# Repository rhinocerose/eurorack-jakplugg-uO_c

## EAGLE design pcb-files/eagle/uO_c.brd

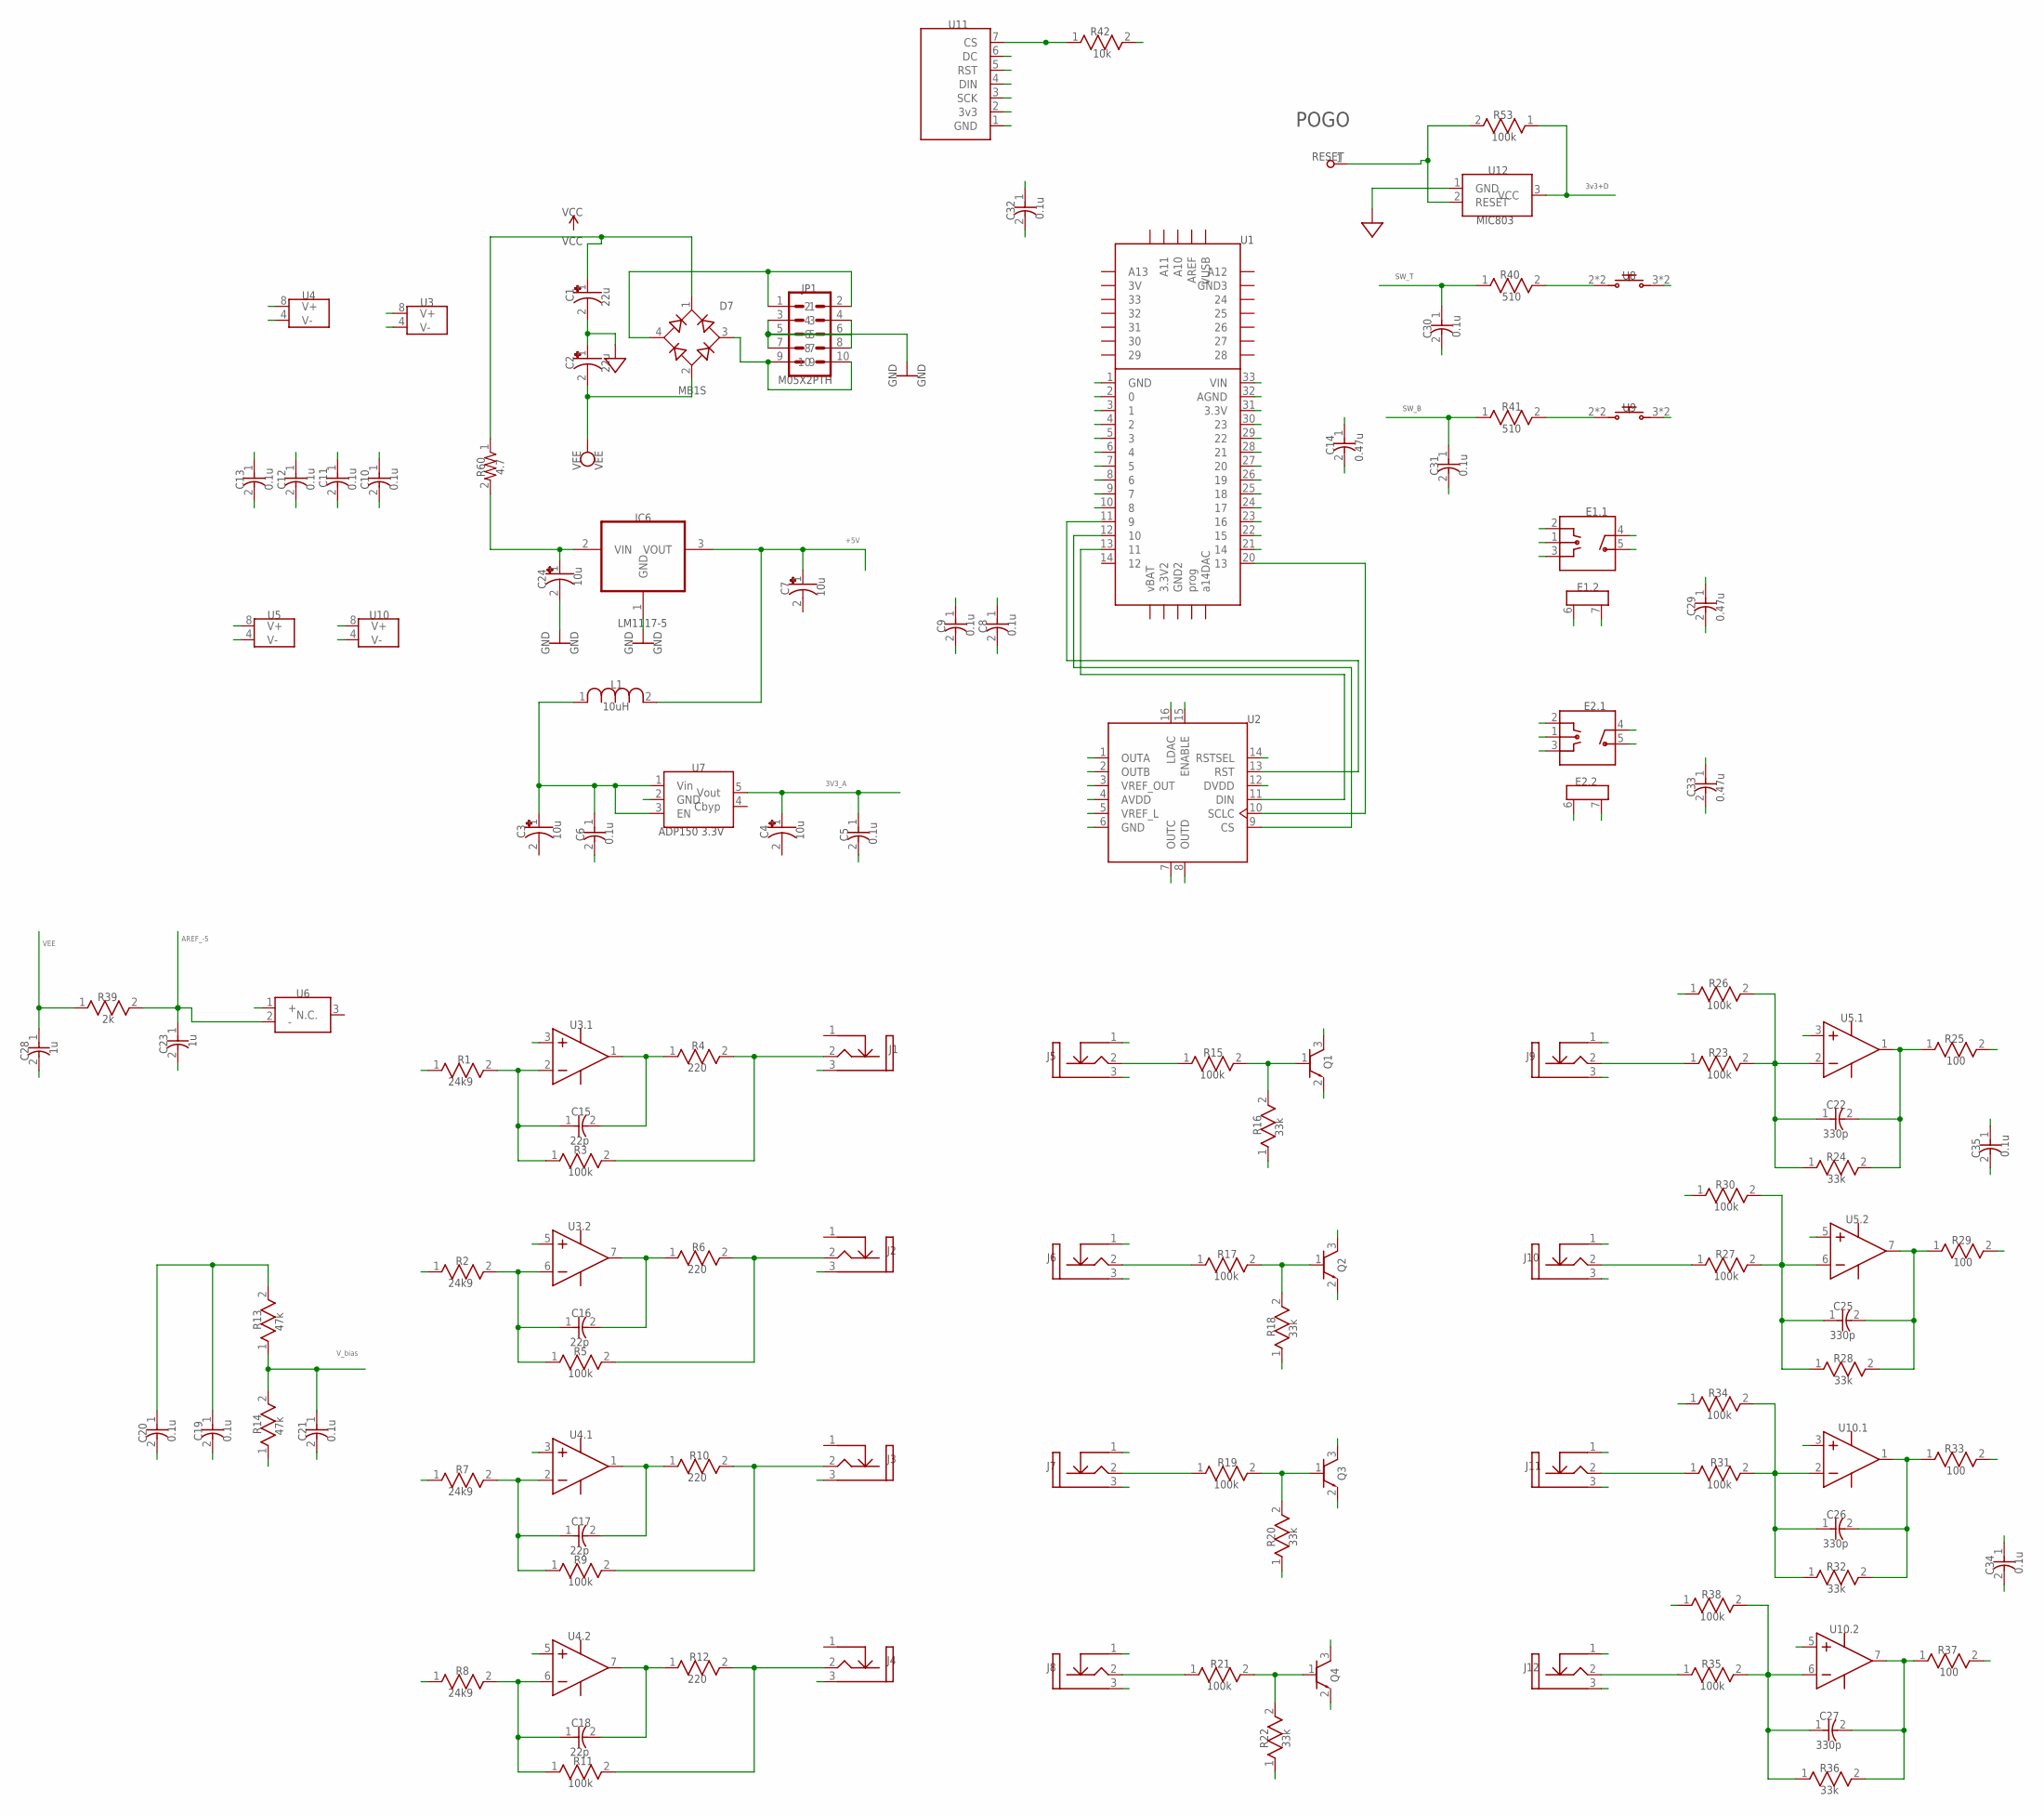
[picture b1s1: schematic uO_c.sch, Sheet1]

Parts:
C1, C2: 22u; CAPAE-5.3X5.3H3
C3, C4, C7, C24: 10u; CAPAE-5.3X5.3H3
C5, C6, C8, C9, C10, C11, C12, C13, C19, C20, C21, C30, C31, C32, C34, C35: 0.1u; CAP_0805
C14, C29, C33: 0.47u; CAP_0805
C15, C16, C17, C18: 22p; CAP_0805
C22, C25, C26, C27: 330p; CAP_0805
C23, C28: 1u; CAP_0805
D7: MB1S; SOP-4/6.5X2.54
E1, E2: PEC11
IC6: LM1117-5; TO252
J1, J2, J3, J4: THONKICONN; THONKICONN_JACK
J5, J6, J7, J8, J9, J10, J11, J12: THONKICONN_20; THONKICONN_JACK
JP1: M05X2PTH; AVR_ICSP
L1: 10uH; RES_1210
Q1, Q2, Q3, Q4: MMBT3904; SOT23
R1, R2, R7, R8: 24k9; RES_0805
R3, R5, R9, R11, R15, R17, R19, R21, R23, R26, R27, R30, R31, R34, R35, R38, R53: 100k; RES_0805
R4, R6, R10, R12: 220; RES_0805
R13, R14: 47k; RES_0805
R16, R18, R20, R22, R24, R28, R32, R36: 33k; RES_0805
R25, R29, R33, R37: 100; RES_0805
R39: 2k; RES_0805
R40, R41: 510; RES_0805
R42: 10k; RES_0805
R60: 4.7; R1206
RESET: RESET; ROUND-ROUND
U1: TEENSY_3.1_EDGE; TEENSY3.1_EDGE
U2: DAC8565; TSSOP-16
U3, U4: OPA2172; SOIC-8/150MIL
U5, U10: MCP6002; SOIC-8/150MIL
U6: LM4040_EM3-5.0; SOT23
U7: ADP150 3.3V; SOT23-5
U8, U9: 6MM_TACTILE_SW; TL1105SP
U11: 1306_DISP_O_C
U12: MIC803; SOT23

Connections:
3V3_A: C4.1 (+), C5.1, C9.1, C34.1, C35.1, U2.4 (AVDD), U5.8 (V+), U7.5 (Vout), U10.8 (V+)
3v3+D: C8.1, C14.1, C32.1, R42.2, R53.1, U1.31 (3.3V), U2.12 (DVDD), U11.2 (3v3), U12.3 (VCC)
+5V: C7.1 (+), IC6.3 (VOUT), L1.2, U1.33 (VIN)
AREF_-5: C23.1, R26.1, R30.1, R34.1, R38.1, R39.2, U6.2 (-)
CS_DAC: U1.12 (10), U2.9 (CS)
CS_OLED: R42.1, U1.10 (8), U11.7 (CS)
CV_1: R25.2, U1.26 (19)
CV_2: R29.2, U1.25 (18)
CV_3: R33.2, U1.27 (20)
CV_4: R37.2, U1.24 (17)
CV_A: R1.1, U2.1 (OUTA)
CV_B: R2.1, U2.2 (OUTB)
CV_C: R7.1, U2.7 (OUTC)
CV_D: R8.1, U2.8 (OUTD)
DC: U1.8 (6), U11.6 (DC)
DOUT: U1.13 (11), U2.11 (DIN), U11.4 (DIN)
ENC_L1: E1.2, U1.29 (22)
ENC_L2: E1.3, U1.28 (21)
ENC_R1: E2.2, U1.22 (15)
ENC_R2: E2.3, U1.23 (16)
GND: C1.2 (-), C2.1 (+), C3.2 (-), C4.2 (-), C5.2, C6.2, C7.2 (-), C8.2, C9.2, C10.2, C11.2, C12.1, C13.1, C14.2, C19.2, C20.2, C21.2, C23.2, C24.2 (-), C28.2, C29.2, C30.2, C31.2, C32.2, C33.2, C34.2, C35.2, E1.1, E1.5, E1.6 (gnd), E1.7 (gnd), E2.1, E2.5, E2.6 (gnd), E2.7 (gnd), IC6.1 (GND), J1.3 (GND), J2.3 (GND), J3.3 (GND), J4.3 (GND), J5.1 (TN), J5.3 (GND), J6.1 (TN), J6.3 (GND), J7.1 (TN), J7.3 (GND), J8.1 (TN), J8.3 (GND), J9.1 (TN), J9.3 (GND), J10.1 (TN), J10.3 (GND), J11.1 (TN), J11.3 (GND), J12.1 (TN), J12.3 (GND), JP1.3, JP1.4, JP1.5, JP1.6, JP1.7, JP1.8, Q1.2 ((E)), Q2.2 ((E)), Q3.2 ((E)), Q4.2 ((E)), R14.1, R16.1, R18.1, R20.1, R22.1, U1.1 (GND), U1.32 (AGND), U2.5 (VREF_L), U2.6 (GND), U2.14 (RSTSEL), U2.15 (ENABLE), U2.16 (LDAC), U5.3 (IN+), U5.4 (V-), U5.5 (IN+), U6.1 (+), U7.2 (GND), U8.3 (2), U8.4 (2), U9.3 (2), U9.4 (2), U10.3 (IN+), U10.4 (V-), U10.5 (IN+), U11.1 (GND), U12.1 (GND)
unnamed: D7.3 (AC2), JP1.9, JP1.10
Net_0: J2.2 (Tip), R5.2, R6.2
Net_1: C16.1, R2.2, R5.1, U3.6 (IN-)
Net_2: C16.2, R6.1, U3.7 (OUT)
Net_3: J3.2 (Tip), R9.2, R10.2
Net_4: C17.1, R7.2, R9.1, U4.2 (IN-)
Net_5: C17.2, R10.1, U4.1 (OUT)
Net_6: J4.2 (Tip), R11.2, R12.2
Net_7: C18.1, R8.2, R11.1, U4.6 (IN-)
Net_8: C18.2, R12.1, U4.7 (OUT)
Net_9: Q2.1 ((B)), R17.2, R18.2
Net_10: Q3.1 ((B)), R19.2, R20.2
Net_11: Q4.1 ((B)), R21.2, R22.2
Net_12: C25.1, R27.2, R28.1, R30.2, U5.6 (IN-)
Net_13: C3.1 (+), C6.1, L1.1, U7.1 (Vin), U7.3 (EN)
Net_18: C26.1, R31.2, R32.1, R34.2, U10.2 (IN-)
Net_19: J1.2 (Tip), R3.2, R4.2
Net_20: C15.1, R1.2, R3.1, U3.2 (IN-)
Net_21: C15.2, R4.1, U3.1 (OUT)
Net_22: C27.1, R35.2, R36.1, R38.2, U10.6 (IN-)
Net_35: Q1.1 ((B)), R15.2, R16.2
Net_39: J8.2 (Tip), R21.1
Net_40: J7.2 (Tip), R19.1
Net_41: J6.2 (Tip), R17.1
Net_42: J5.2 (Tip), R15.1
Net_43: C22.1, R23.2, R24.1, R26.2, U5.2 (IN-)
Net_48: C27.2, R36.2, R37.1, U10.7 (OUT)
Net_49: C26.2, R32.2, R33.1, U10.1 (OUT)
Net_50: C25.2, R28.2, R29.1, U5.7 (OUT)
Net_51: C22.2, R24.2, R25.1, U5.1 (OUT)
Net_52: J9.2 (Tip), R23.1
Net_53: J10.2 (Tip), R27.1
Net_54: J11.2 (Tip), R31.1
Net_55: J12.2 (Tip), R35.1
Net_73: C24.1 (+), IC6.2 (VIN), R60.2
Net_75: R41.2, U9.1, U9.2 (1)
Net_76: R40.2, U8.1, U8.2 (1)
Net_88: R53.2, RESET.1, U12.2 (RESET)
Net_107: D7.4 (AC1), JP1.1, JP1.2
RST: U1.9 (7), U11.5 (RST)
RST_DAC: U1.11 (9), U2.13 (RST)
SCK: U1.20 (13), U2.10 (SCLC), U11.3 (SCK)
SW_B: C31.1, R41.1, U1.6 (4)
SW_L: C29.1, E1.4, U1.30 (23)
SW_R: C33.1, E2.4, U1.21 (14)
SW_T: C30.1, R40.1, U1.7 (5)
TR1: Q1.3 ((C)), U1.2 (0)
TR2: Q2.3 ((C)), U1.3 (1)
TR3: Q3.3 ((C)), U1.4 (2)
TR4: Q4.3 ((C)), U1.5 (3)
VCC: C1.1 (+), C10.1, C11.1, D7.1 (+), R60.1, U3.8 (V+), U4.8 (V+)
VEE: C2.2 (-), C12.2, C13.2, C28.1, D7.2 (-), R39.1, U3.4 (V-), U4.4 (V-)
VREF_2v5: C19.1, C20.1, R13.2, U2.3 (VREF_OUT)
V_bias: C21.1, R13.1, R14.2, U3.3 (IN+), U3.5 (IN+), U4.3 (IN+), U4.5 (IN+)

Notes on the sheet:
SW_T
SW_B
3v3+D
POGO
22u
10u
0.1u
C10
C11
C12
C13
C14
0.47u
C15
22p
C16
C17
C18
C19
C20
C21
C22
330p
C23
C24
C25
C26
C27
C28
C29
C30
C31
C32
MB1S
E1.1
E1.2
E2.1
E2.2
GND
IC6

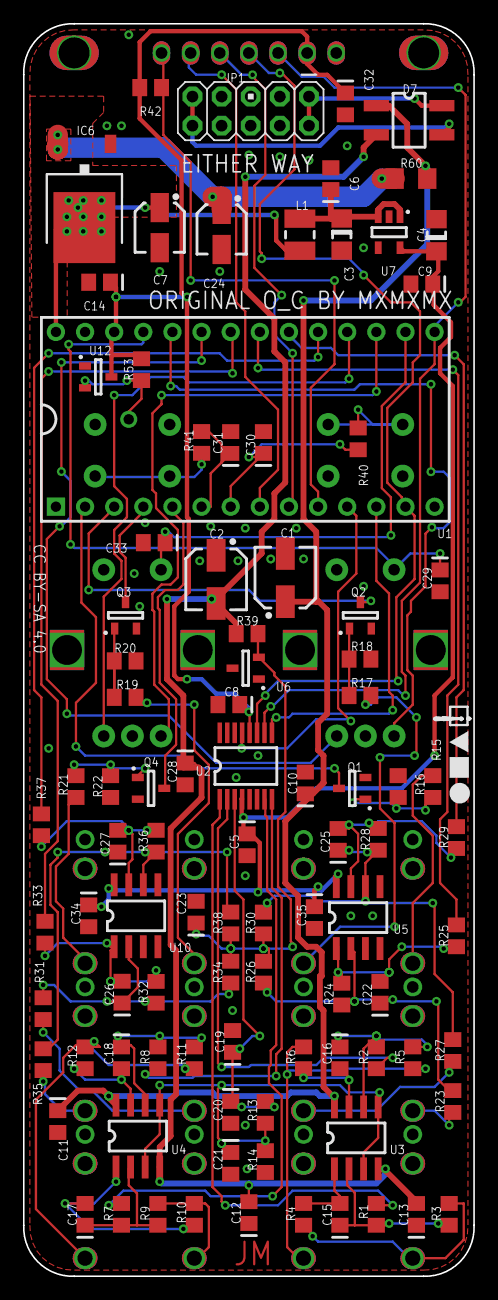
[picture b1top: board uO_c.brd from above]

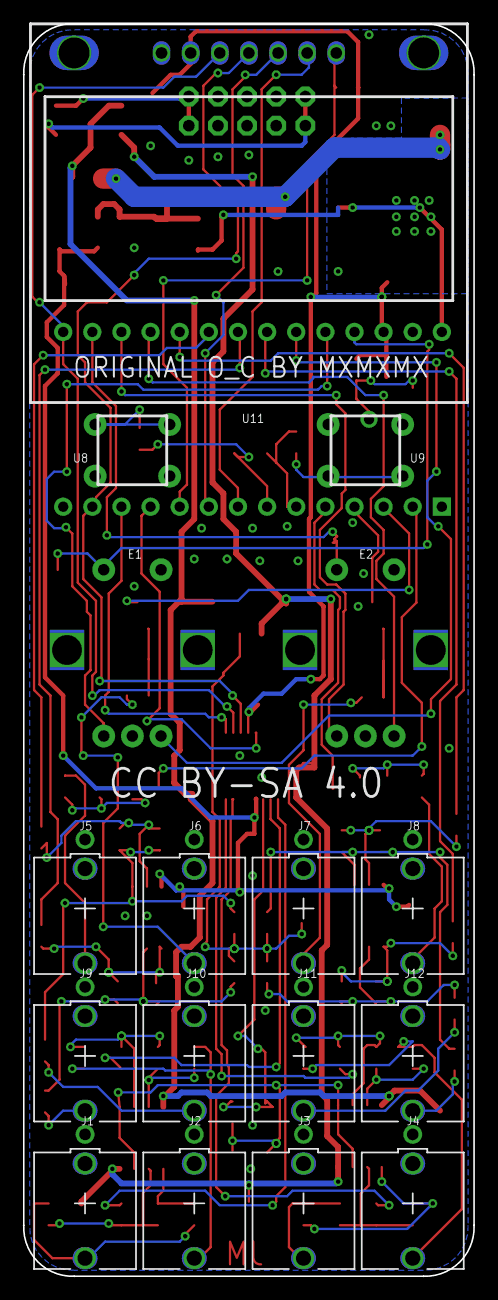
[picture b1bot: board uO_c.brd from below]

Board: 2 copper layers, 39.3 x 109.2 mm, 116 parts (17 on the bottom side), 75 nets.

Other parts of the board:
Pad1, Pad2: PAD; Pad

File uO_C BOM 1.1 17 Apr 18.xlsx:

Quantity | Value | Name | RefDes | Mouser | Other | Notes
 |  |  |  | Capacitors
4.0 | 22p | CAP_0805 | C15, C16, C17, C18 | 77-VJ0805A220GXAPBC |  | or 18p
4.0 | 560p | CAP_0805 | C22, C25, C26, C27 | 77-VJ0805A561JXAAC
16.0 | 0.1u | CAP_0805 | C5, C6, C8, C9, C10, C11, C12, C13, C19, C20, C21, C30, C31, C32, C34, C35 | 80-C0805C104K5R
3.0 | 0.47u | CAP_0805 | C14, C29, C33 | 581-080516C474K
2.0 | 1u | CAP_0805 | C23, C28 | 81-GCM21BR71H105KA3L
2.0 | 10u | CAP_1206 | C3, C4 | 81-GRM319R61E106KA2D
2.0 | 22u | CPOL-USC | C1, C2 | 667-EEE-FK1V220R |  | 35V
2.0 | 10u | CPOL-USC | C7, C24 | 667-EEE-FK1E100R |  | 25V
 |  |  |  | Resistors
1.0 | 4.7 | R-US_R1206 | R60 | 660-RK73B2BTTDD4R7J
4.0 | 100.0 | RES_0805 | R25, R29, R33, R37 | 660-RK73H2ATTD1000F
4.0 | 220.0 | RES_0805 | R4, R6, R10, R12 | 279-CPF0805B220RE1 |  | 0.001 | 0.1% Not REALY needed, It will just result in less trimming adjustment
2.0 | 510.0 | RES_0805 | R40, R41 | 603-RC0805JR-07510RL
1.0 | 2k | RES_0805 | R39 | 660-RK73H2ATTE2001F
1.0 | 10k | RES_0805 | R42 | 660-RK73H2ATTD1002F
4.0 | 24k9 | RES_0805 | R1, R2, R7, R8 | 756-PCF0805R-24K9BT1 |  | 0.001 | 0.1% Not REALY needed, It will just result in less trimming adjustment
8.0 | 33k | RES_0805 | R16, R18, R20, R22, R24, R28, R32, R36 | 660-RK73H2ATTD3302F
2.0 | 47k | RES_0805 | R13, R14 | 660-RK73H2ATTD4702F
4.0 | 75k | RES_0805 | R26, R30, R34, R38 | 660-RK73H2ATTD7502F
13.0 | 100k | RES_0805 | R3, R5, R9, R11, R15, R17, R19, R21, R23, R27, R31, R35, R53 | 279-CPF0805B100KE |  | 0.001 | 0.1% Not REALY needed, It will just result in less trimming adjustment
 |  |  |  | Inductor
1.0 | 10uH |  | L1 | 963-LB3218T100K
 |  |  |  | Semiconductors
1.0 |  | DAC8565 | U2 | 595-DAC8565ICPW
1.0 |  | LM4040_EM3-5.0 | U6 | 926-LM4040DIM350NOPB
1.0 | ADP150 3.3V | ADP150 3.3V | U7 | 584-ADP150AUJZ-3.3R7
1.0 |  | Teensy 3.2 | U1 | 485-2756 |  | cheapest at osh park
1.0 | MB1S | MB1S | D7 | 512-MB1S
2.0 |  | MCP6002 | U5, U10 | 579-MCP6002T-I/SN
2.0 |  | OPA2172 | U3, U4 | 595-OPA2172IDR
1.0 |  | MIC803 | U12 | MIC803-26D4VM3-TR |  | supervisor option
4.0 |  | MMBT3904 | Q1, Q2, Q3, Q4 | 512-MMBT3904
1.0 | LM1117-5 | REG1117T | IC6 | 511-LD1117DT50C-TR
 |  |  |  | Controls
2.0 |  | PEC11 | E1, E2 | 858-EN11-HSM1BF20
2.0 |  | 6mm Tactile SW | U8, U9 | 612-TL1105SPF100Q
12.0 |  | Thonkiconn | J1, J2, J3, J4, J5, J6, J7, J8, J9, J10, J11, J12 |  |  | Thonk/Synthcube/Erthenvar
 |  |  |  | Other Hardware
2.0 |  | Tact Caps |  | 612-1R-RD |  | colors, change last letters. BLK, WHT
2.0 |  |  |  | 481-0007 |  | Extra M7 Nuts for Mounting
1.0 | 10 pin power header | M05X2PTH | JP1 | 49-67996-410HLF
2.0 |  |  |  | 761-M0505-25-N |  | M2.5 Spacer
4.0 |  |  |  | 534-29301 |  | M2.5 Screws, 6mm
6.0 |  |  |  |  | Amazon | washer, Nylon M2.5. These need to end up to be 3mm thick so double them up, etc.
1.0 |  |  | RESET POGO PIN | 855-P70-2300045R
1.0 | 7 pin 128x64 OLED |  |  | ebay, amazon, alibaba, etc.

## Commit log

2025-08-10 Kicad

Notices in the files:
pcb-files/eagle/uO_c.brd:
CC BY-SA 4.0
